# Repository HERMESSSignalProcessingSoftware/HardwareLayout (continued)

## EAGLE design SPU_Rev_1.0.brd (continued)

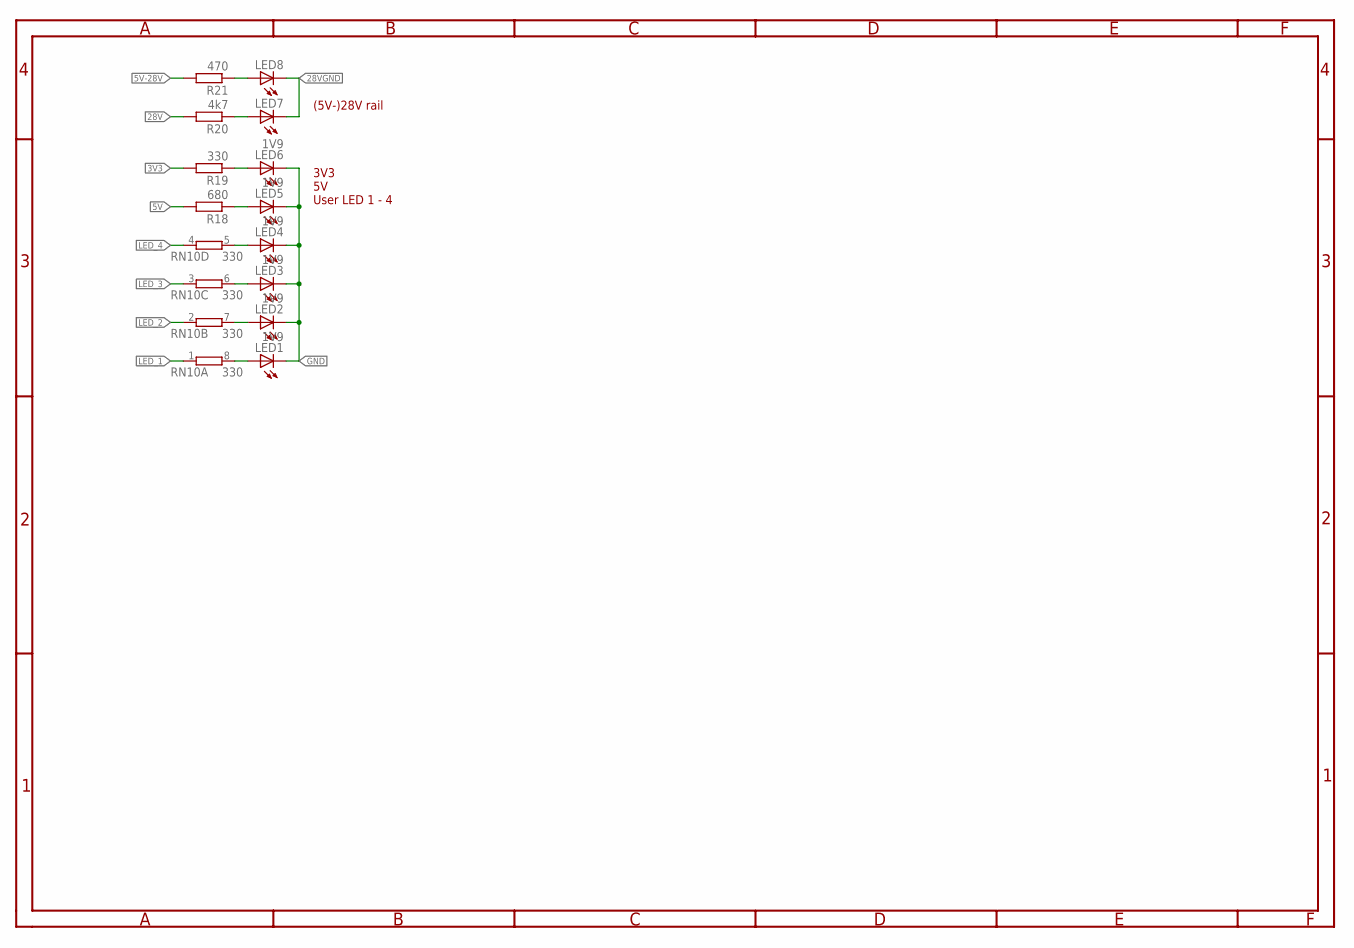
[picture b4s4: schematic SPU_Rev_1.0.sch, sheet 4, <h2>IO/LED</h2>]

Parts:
LED1, LED2, LED3, LED4, LED5, LED6: 1V9; CHIP-LED0603
LED7, LED8: LEDCHIP-LED0603; CHIP-LED0603
R18: 680; R0805
R19: 330; R0805
R20: 4k7; R0805
R21: 470; R0805
RN10: 330; EXBS8V

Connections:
3V3: R19.2; also elsewhere on the board
5V: R18.2; also elsewhere on the board
5V-28V: R21.2; also elsewhere on the board
28V: R20.2; also elsewhere on the board
28VGND: LED7.C, LED8.C; also elsewhere on the board
GND: LED1.C, LED2.C, LED3.C, LED4.C, LED5.C, LED6.C; also elsewhere on the board
LED_1: RN10.1; also elsewhere on the board
LED_2: RN10.2 (1); also elsewhere on the board
LED_3: RN10.3 (1); also elsewhere on the board
LED_4: RN10.4 (1); also elsewhere on the board
unnamed: LED1.A, RN10.8 (2)
unnamed: LED2.A, RN10.7 (2)
unnamed: LED3.A, RN10.6 (2)
unnamed: LED4.A, RN10.5 (2)
unnamed: LED5.A, R18.1
unnamed: LED6.A, R19.1
unnamed: LED7.A, R20.1
unnamed: LED8.A, R21.1

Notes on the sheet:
(5V-)28V rail 3V3 5V User LED 1 - 4

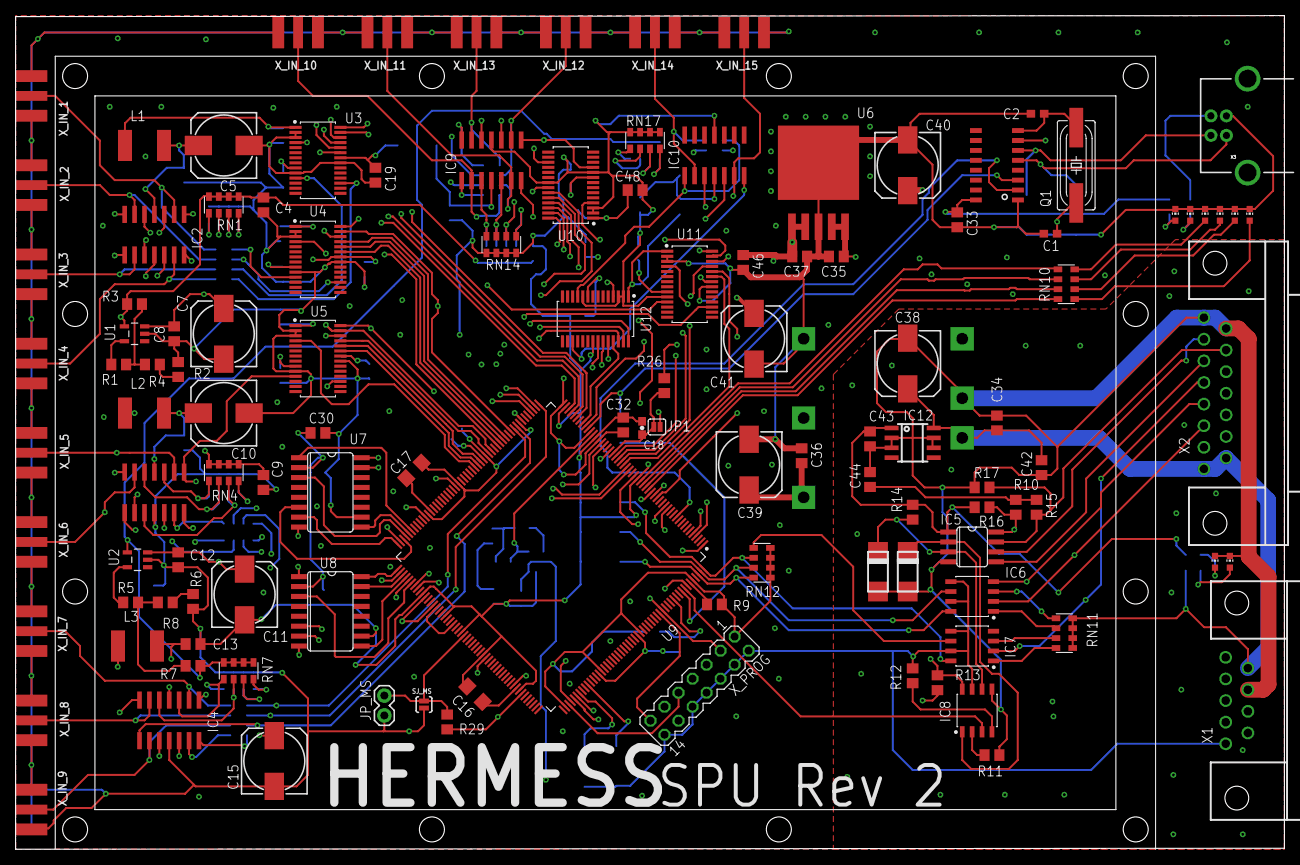
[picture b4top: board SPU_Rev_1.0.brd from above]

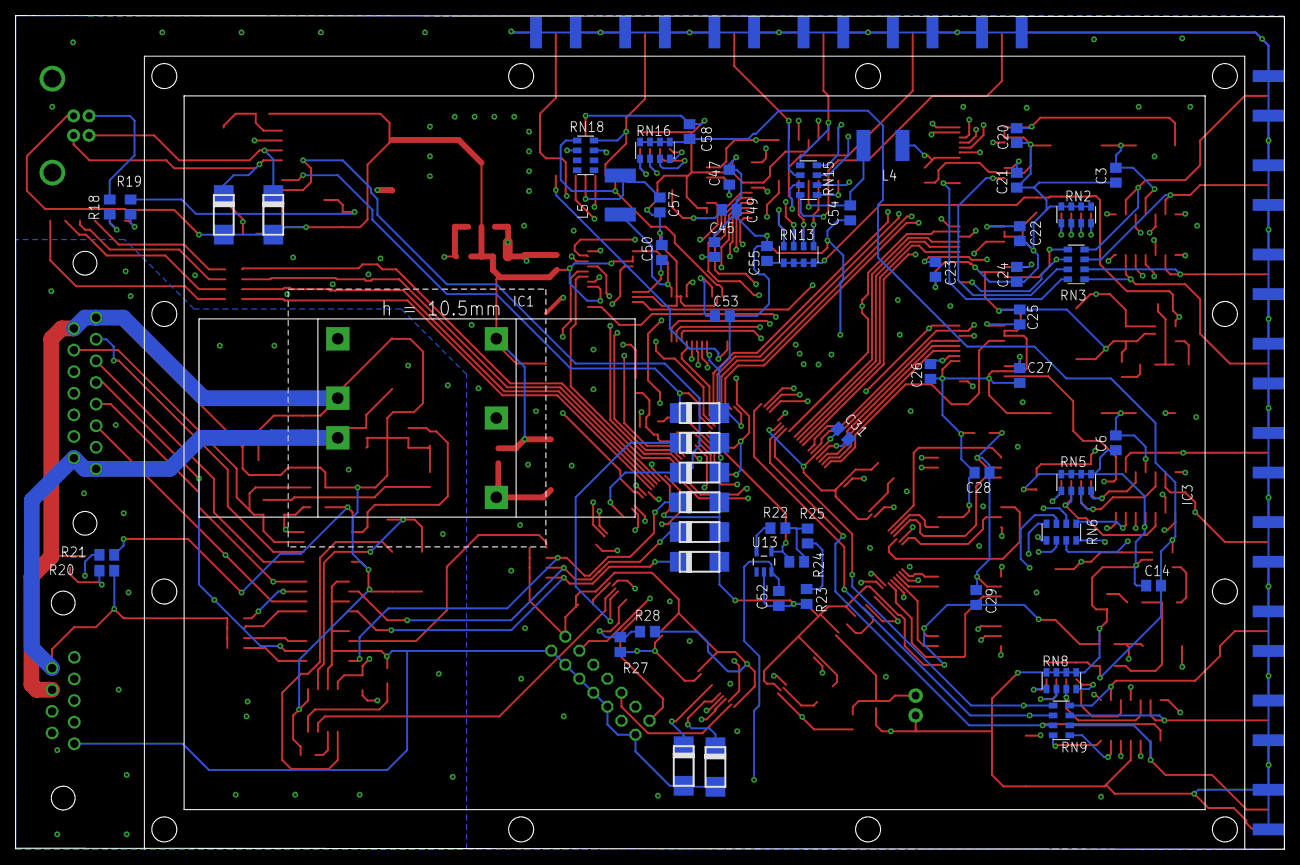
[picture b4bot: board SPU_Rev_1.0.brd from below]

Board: 4 copper layers, 162.6 x 106.8 mm, 176 parts (58 on the bottom side), 188 nets.

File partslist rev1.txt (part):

Partlist

Exported from Blade.brd at 25.03.2020 16:29

EAGLE Version 9.6.0 Copyright (c) 1988-2020 Autodesk, Inc.

Assembly variant: 

Part     Value                      Package                    Library              Position (mil)        Orientation

C1       22p                        C0603                      rcl                  (5220 3105)           R180
C2       22p                        C0603                      rcl                  (5155 3710)           R180
C3       10n                        C0805                      rcl                  (850 3400)            MR90
C4       10u                        C0805                      rcl                  (1250 3250)           R90
C5       10u                        153CLV-0810                rcl                  (1050 3550)           R180
C6       10n                        C0805                      rcl                  (850 2050)            MR90
C7       4u7                        153CLV-0810                rcl                  (1050 2600)           R90
C8       10n                        C0805                      rcl                  (800 2600)            R90
C9       10u                        C0805                      rcl                  (1250 1850)           R90
C10      10u                        153CLV-0810                rcl                  (1050 2200)           R180
C11      4u7                        153CLV-0810                rcl                  (1155 1285)           R90
C12      10n                        C0805                      rcl                  (820 1460)            R90
C13      10n                        C0805                      rcl                  (895 1035)            R180
C14      10u                        C0805                      rcl                  (660 1330)            MR0
C15      10u                        153CLV-0810                rcl                  (1305 445)            R90
C16      2.2u                       C1206                      rcl                  (2317.67766 782.32222) R315
C17      2.2u                       C1206                      rcl                  (2009.39333 1910.60655) R225
C18      100n                       0603-CAP                   aSparkFun            (3160 2125)           R90
C19      100n                       C0805                      rcl                  (1815 3400)           R270
C20      100n                       C0805                      rcl                  (1350 3600)           MR270
C21      1u                         C0805                      rcl                  (1350 3375)           MR270
C22      100n                       C0805                      rcl                  (1335 3105)           MR270
C23      100n                       C0805                      rcl                  (1760 2925)           MR270
C24      1u                         C0805                      rcl                  (1350 2900)           MR270
C25      100n                       C0805                      rcl                  (1335 2685)           MR90
C26      100n                       C0805                      rcl                  (1785 2410)           MR270
C27      1u                         C0805                      rcl                  (1335 2390)           MR270
C28      100n                       C0805                      rcl                  (1525 1900)           MR180
C29      100n                       C0805                      rcl                  (1555 1270)           MR270
C30      100n                       C0805                      rcl                  (1525 2100)           R0
C31      100n                       C0805                      rcl                  (2225 2095)           MR135
C32      100n                       C0805                      rcl                  (3065 2140)           R90
C33      100n                       C0805                      rcl                  (4750 3175)           R270
C34      100n                       C0805                      rcl                  (4950 2150)           R270
C35      100n                       C0805                      rcl                  (4140 2990)           R0
C36      100n                       C0805                      rcl                  (3965 1985)           R270
C37      100n                       C0805                      rcl                  (3955 2990)           R180
C38      10u                        153CLV-0810                rcl                  (4500 2450)           R270
C39      10u                        153CLV-0810                rcl                  (3700 1940)           R270
C40      10u                        153CLV-0810                rcl                  (4500 3450)           R270
C41      10u                        153CLV-0810                rcl                  (3725 2575)           R90
C42      100n                       C0805                      rcl                  (5175 1925)           R90
C43      100n                       C0805                      rcl                  (4310 2070)           R270
C44      ~0                         C0805                      rcl                  (4310 1865)           R90
C45      100n                       C0805                      rcl                  (2875 3025)           MR90
C46      100n                       C0805                      rcl                  (3670 2960)           R270
C47      1u                         C0805                      rcl                  (2800 3390)           MR90
C48      100n                       C0805                      rcl                  (3125 3325)           R0
C49      100n                       C0805                      rcl                  (2800 3225)           MR0
C50      1u                         C0805                      rcl                  (3140 3010)           MR90
C52      10n                        C0805                      rcl                  (2550 1265)           MR90
C53      1u                         C0805                      rcl                  (2835 2690)           MR0
C54      10n                        C0805                      rcl                  (2190 3210)           MR90
C55      10u                        C0805                      rcl                  (2610 3005)           MR270
C57      10n                        C0805                      rcl                  (3150 3250)           MR90
C58      10u                        C0805                      rcl                  (3000 3620)           MR270
D1       3V6                        DMELF                      diodes               (5100 3200)           MR90
D2       3V6                        DMELF                      diodes               (5350 3200)           MR90
D3       3V6                        DMELF                      diodes               (2950 2200)           MR180
D4       3V6                        DMELF                      diodes               (2950 1900)           MR180
D5       6V                         DMELF                      diodes               (4500 1400)           R90
D6       6V                         DMELF                      diodes               (4350 1400)           R90
D7       3V6                        DMELF                      diodes               (2950 1750)           MR180
D8       3V6                        DMELF                      diodes               (2950 1450)           MR180
D9       3V6                        DMELF                      diodes               (2950 1600)           MR180
D10      3V6                        DMELF                      diodes               (2950 2050)           MR180
IC1      THN10-2411WIR              THL_20WI_SERIES            traco_thl_tel_series (4375 2175)           MR90
IC2      MCP6064-E/SL               SO14                       linear               (700 3100)            R180
IC3      MCP6064-E/SL               SO14                       linear               (700 1800)            R180
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
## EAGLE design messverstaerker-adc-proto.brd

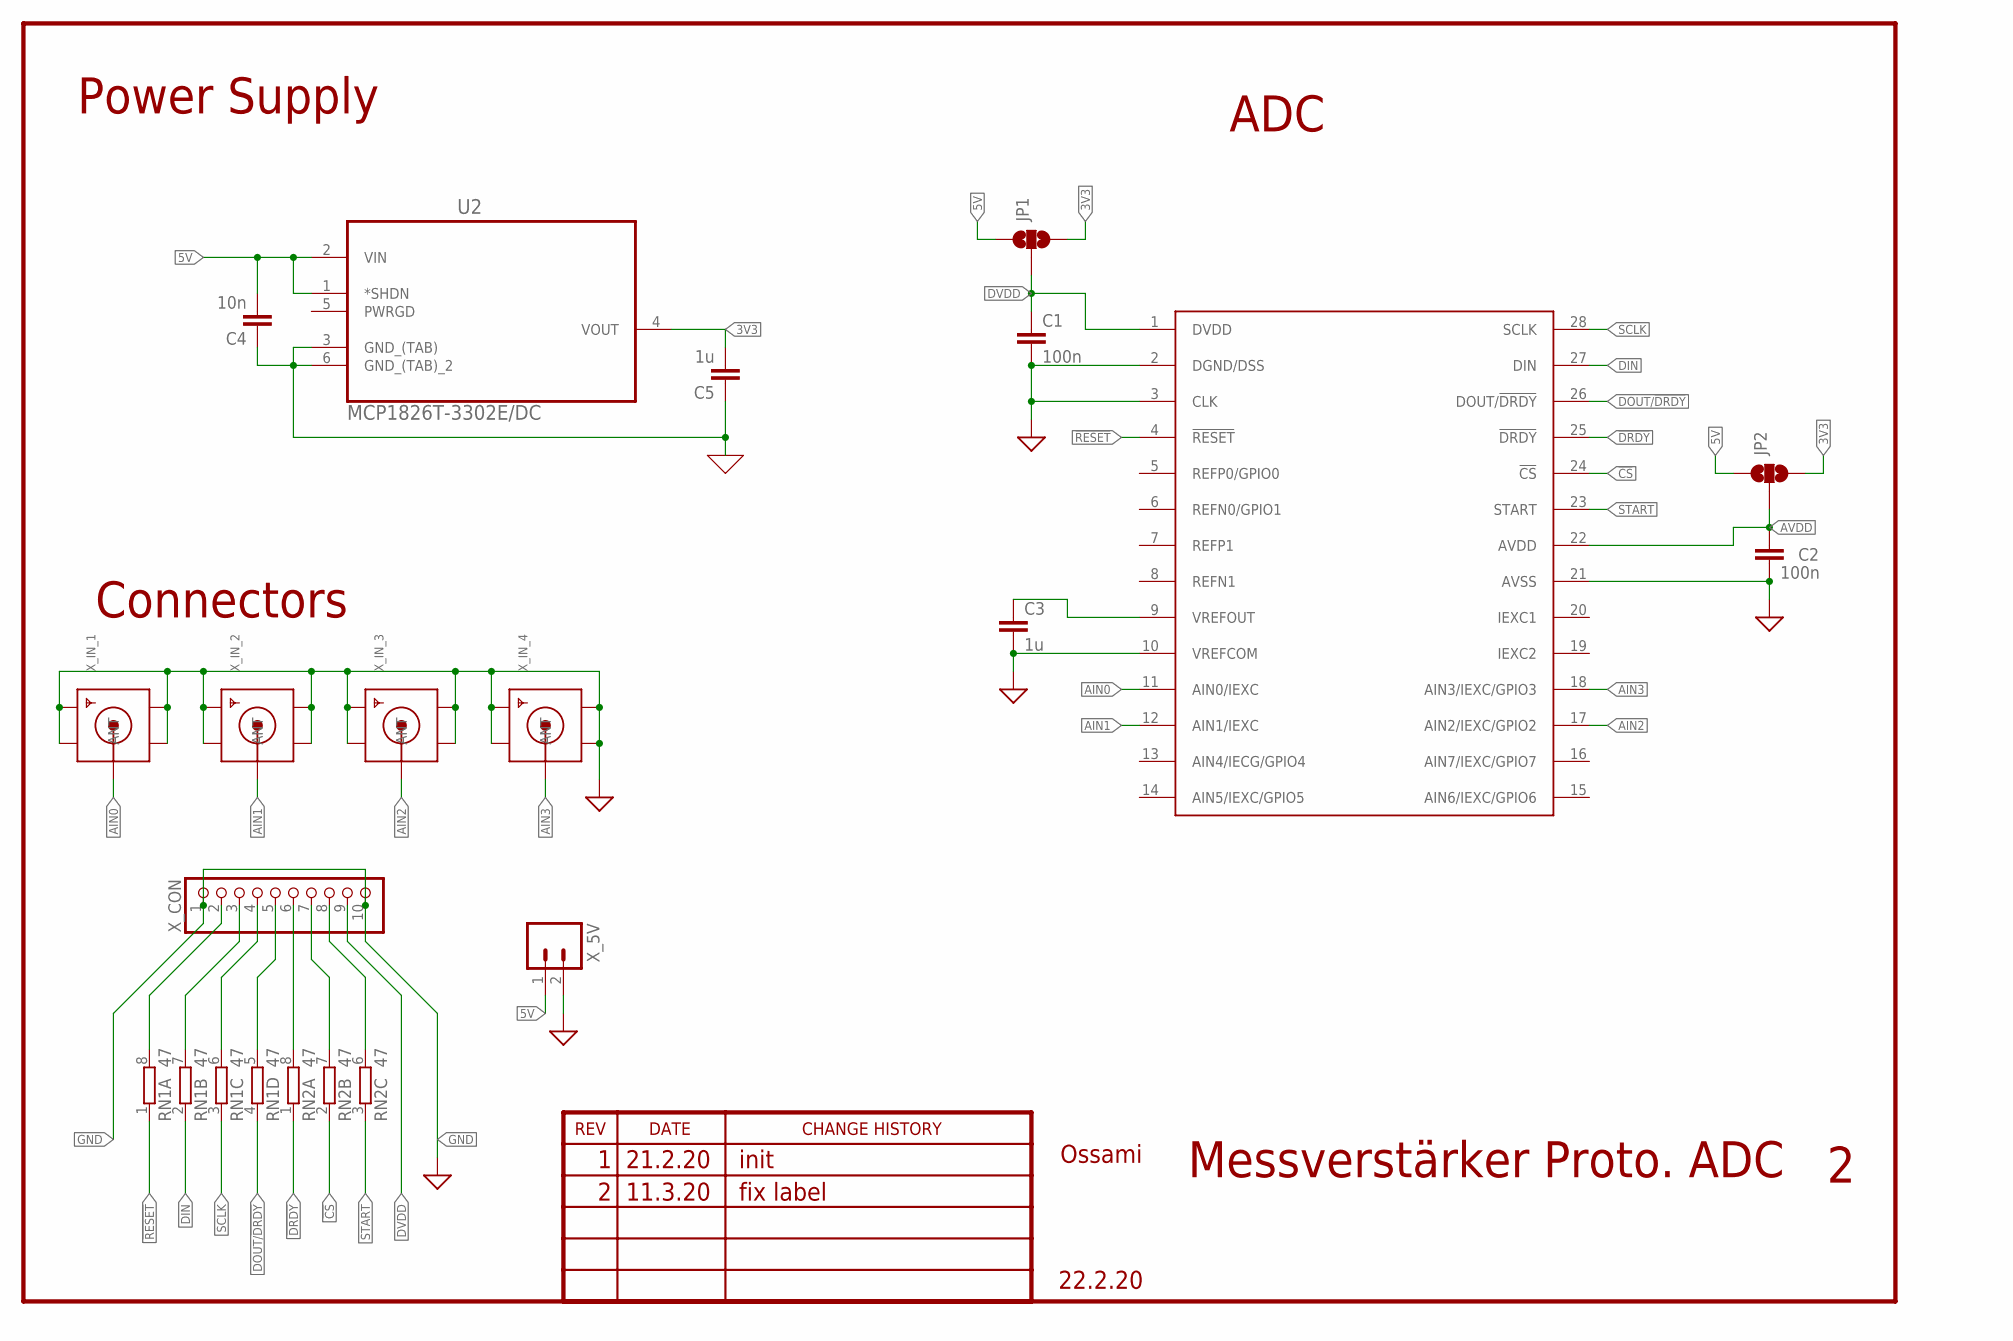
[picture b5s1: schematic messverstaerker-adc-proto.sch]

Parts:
C1, C2: 100n; C0805
C3, C5: 1u; C0805
C4: 10n; C0805
JP1, JP2: JUMPER-SMT_3_NO_NO-SILK; SMT-JUMPER_3_NO_NO-SILK
RN1, RN2: 47; EXBS8V
U1: ADS1148QPWRQ1; TSSOP28
U2: MCP1826T-3302E/DC; SOT230P700X180-6N
X_5V: M02LOCK; 1X02_LOCK
X_CON: PINHD-1X10; 1X10-BIG
X_IN_1, X_IN_2, X_IN_3, X_IN_4: SMACONNECTOR_EDGE; SMA_EDGELAUNCH

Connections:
0: C4.1, C5.1, U2.3 (GND_(TAB)), U2.6 (GND_(TAB)_2)
3V3: C5.2, JP1.3, JP2.3, U2.4 (VOUT)
5V: C4.2, JP1.1, JP2.1, U2.1 (*SHDN), U2.2 (VIN), X_5V.1
!CS: RN2.2 (1), U1.24 (!CS)
!DRDY: RN2.1, U1.25 (!DRDY)
!RESET: RN1.1, U1.4 (!RESET)
AIN0: U1.11 (AIN0/IEXC), X_IN_1.P (ANT)
AIN1: U1.12 (AIN1/IEXC), X_IN_2.P (ANT)
AIN2: U1.17 (AIN2/IEXC/GPIO2), X_IN_3.P (ANT)
AIN3: U1.18 (AIN3/IEXC/GPIO3), X_IN_4.P (ANT)
AVDD: C2.1, JP2.2, U1.22 (AVDD)
DIN: RN1.2 (1), U1.27 (DIN)
DOUT/!DRDY: RN1.4 (1), U1.26 (DOUT/!DRDY)
DVDD: C1.1, JP1.2, U1.1 (DVDD), X_CON.9
GND: C1.2, C2.2, C3.2, U1.2 (DGND/DSS), U1.3 (CLK), U1.10 (VREFCOM), U1.21 (AVSS), X_5V.2, X_CON.1, X_CON.10, X_IN_1.GND@1 (GND4), X_IN_1.GND@2 (GND3), X_IN_1.GND@3 (GND2), X_IN_1.GND@4 (GND1), X_IN_2.GND@1 (GND4), X_IN_2.GND@2 (GND3), X_IN_2.GND@3 (GND2), X_IN_2.GND@4 (GND1), X_IN_3.GND@1 (GND4), X_IN_3.GND@2 (GND3), X_IN_3.GND@3 (GND2), X_IN_3.GND@4 (GND1), X_IN_4.GND@1 (GND4), X_IN_4.GND@2 (GND3), X_IN_4.GND@3 (GND2), X_IN_4.GND@4 (GND1)
unnamed: RN1.5 (2), X_CON.5
unnamed: C3.1, U1.9 (VREFOUT)
unnamed: RN2.8 (2), X_CON.6
unnamed: RN2.7 (2), X_CON.7
unnamed: RN2.6 (2), X_CON.8
unnamed: RN1.6 (2), X_CON.4
unnamed: RN1.7 (2), X_CON.3
unnamed: RN1.8 (2), X_CON.2
SCLK: RN1.3 (1), U1.28 (SCLK)
START: RN2.3 (1), U1.23 (START)

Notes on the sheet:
Messverstärker Proto. ADC
Ossami
22.2.20
1 21.2.20 init
Power Supply
Connectors
ADC
2 11.3.20 fix label

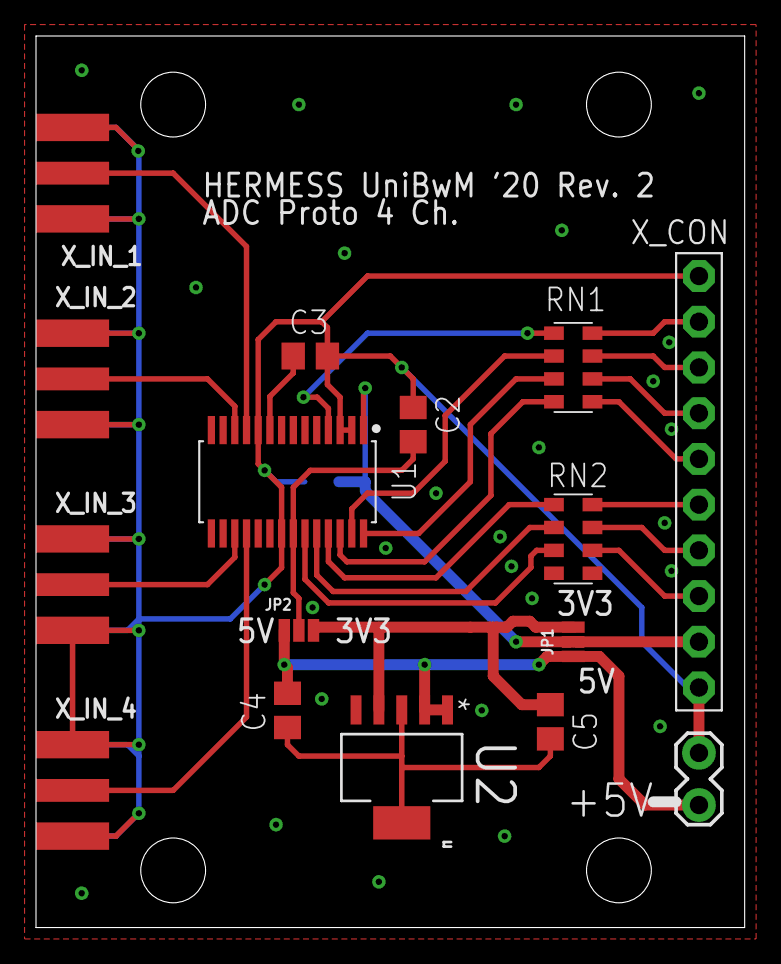
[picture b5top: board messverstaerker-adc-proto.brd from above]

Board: 2 copper layers, 39.4 x 49.5 mm, 17 parts (1 on the bottom side), 25 nets.

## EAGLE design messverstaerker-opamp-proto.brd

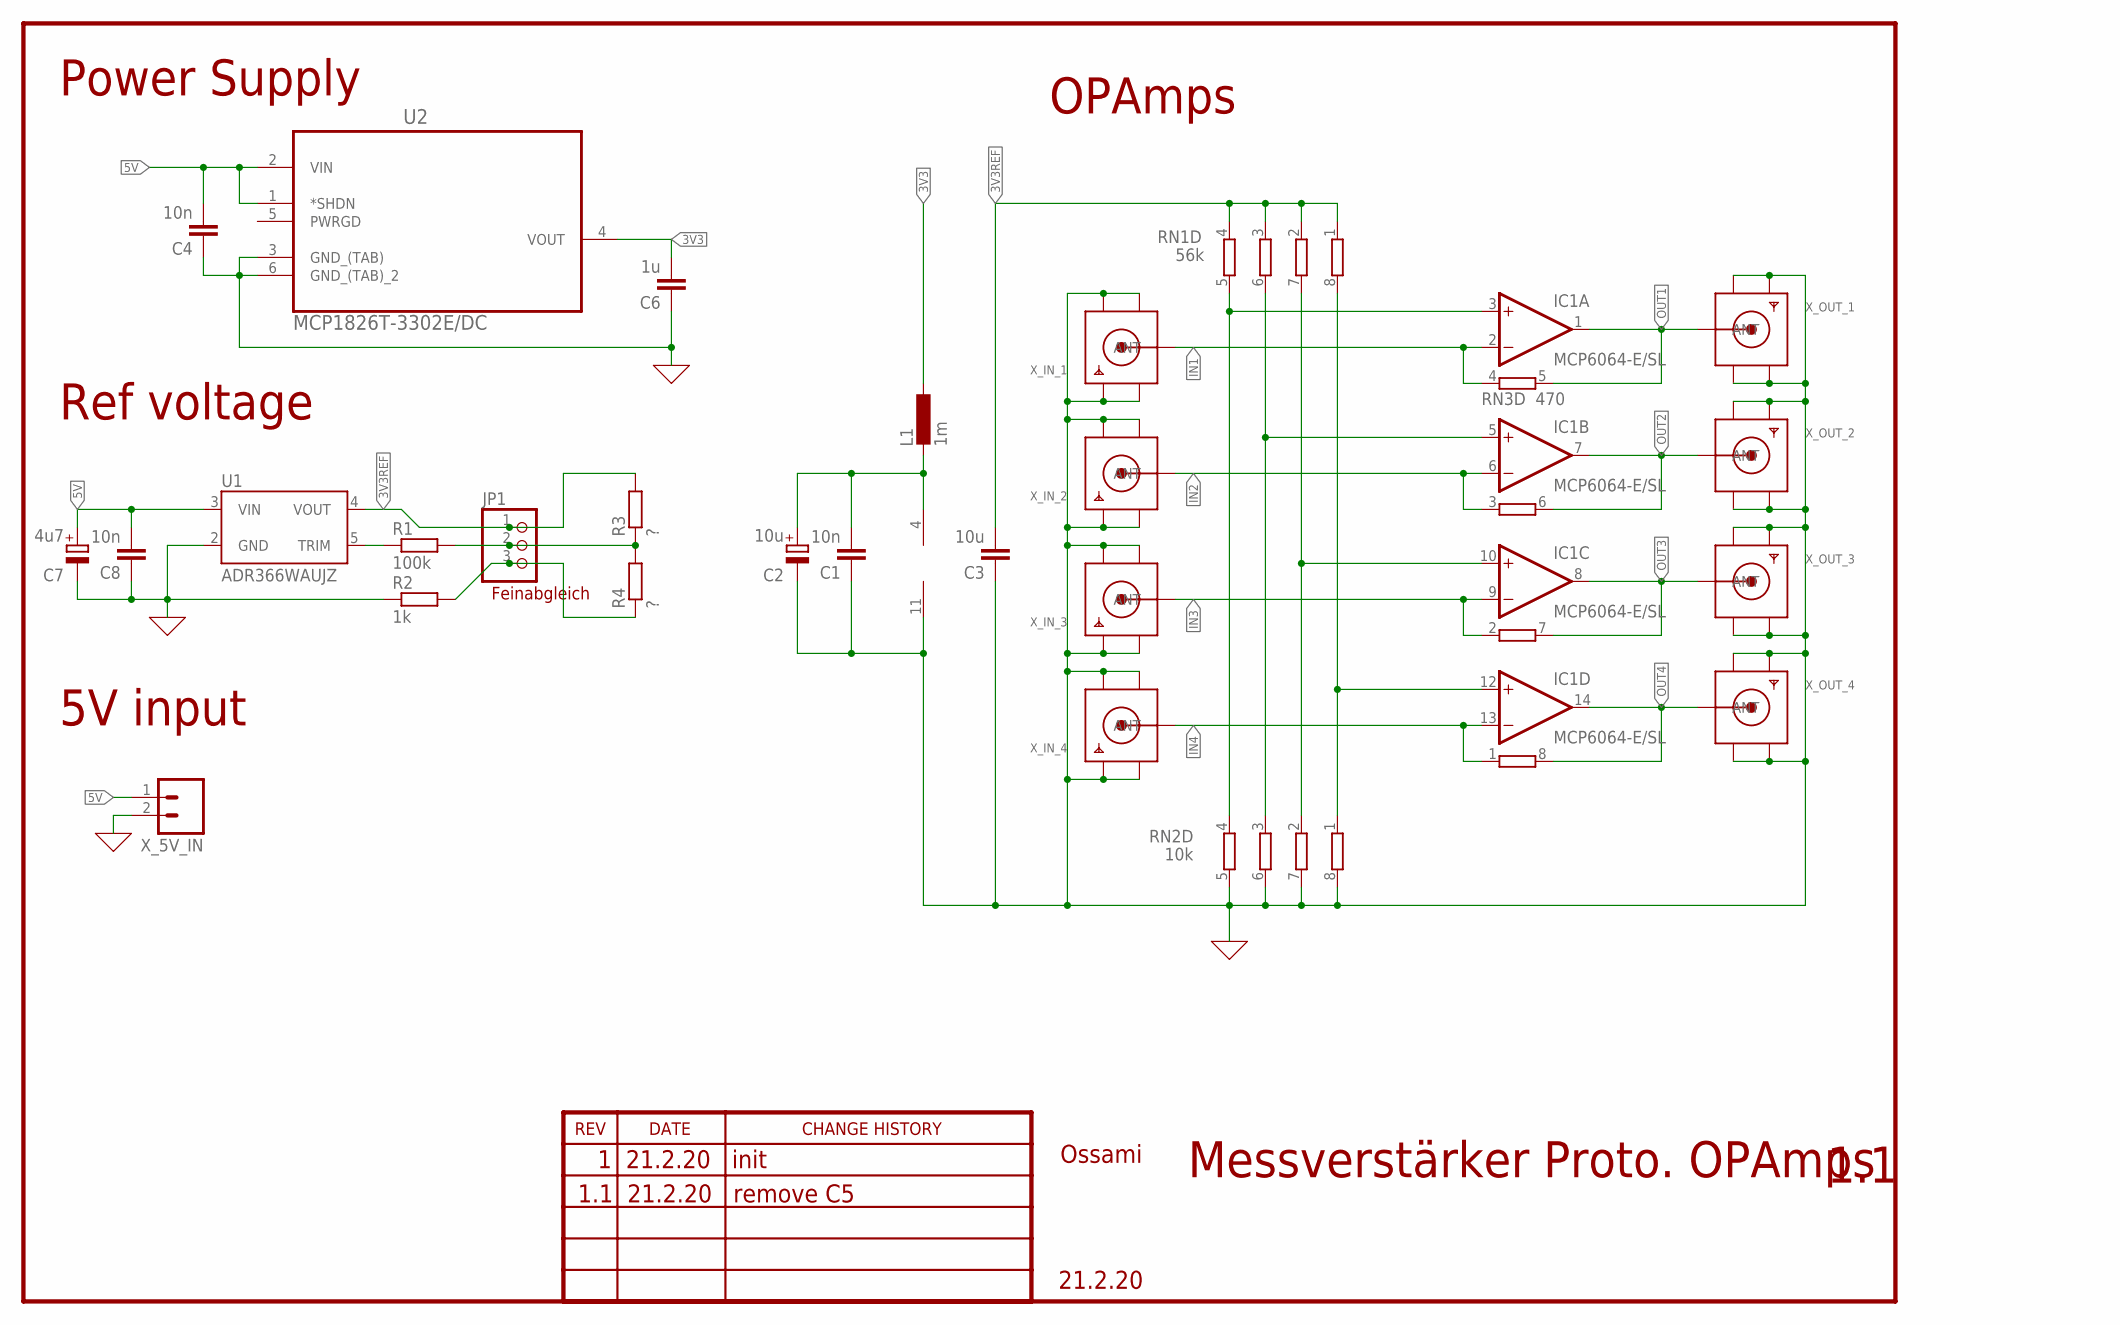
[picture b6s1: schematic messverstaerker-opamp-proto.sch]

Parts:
C1, C4, C8: 10n; C0805
C2: 10u; 153CLV-0810
C3: 10u; C0805
C6: 1u; C0805
C7: 4u7; 153CLV-0810
IC1: MCP6064-E/SL; SO14
JP1: PINHD-1X3; 1X03
L1: 1m; L5650M
R1: 100k; R0805
R2: 1k; R0805
R3, R4: ?; R0805
RN1: 56k; EXBS8V
RN2: 10k; EXBS8V
RN3: 470; EXBS8V
U1: ADR366WAUJZ; SOT23-5
U2: MCP1826T-3302E/DC; SOT230P700X180-6N
X_5V_IN: M02LOCK; 1X02_LOCK
X_IN_1, X_IN_2, X_IN_3, X_IN_4: SMACONNECTOR_EDGE; SMA_EDGELAUNCH
X_OUT_1, X_OUT_2, X_OUT_3, X_OUT_4: SMACONNECTOR_EDGE; SMA_EDGELAUNCH

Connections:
0: C1.1, C2.-, C3.1, C4.1, C6.1, C7.-, C8.1, IC1.11 (V-), R2.1, RN2.5 (2), RN2.6 (2), RN2.7 (2), RN2.8 (2), U1.2 (GND), U2.3 (GND_(TAB)), U2.6 (GND_(TAB)_2), X_5V_IN.2, X_IN_1.GND@1 (GND4), X_IN_1.GND@2 (GND3), X_IN_1.GND@3 (GND2), X_IN_1.GND@4 (GND1), X_IN_2.GND@1 (GND4), X_IN_2.GND@2 (GND3), X_IN_2.GND@3 (GND2), X_IN_2.GND@4 (GND1), X_IN_3.GND@1 (GND4), X_IN_3.GND@2 (GND3), X_IN_3.GND@3 (GND2), X_IN_3.GND@4 (GND1), X_IN_4.GND@1 (GND4), X_IN_4.GND@2 (GND3), X_IN_4.GND@3 (GND2), X_IN_4.GND@4 (GND1), X_OUT_1.GND@1 (GND4), X_OUT_1.GND@2 (GND3), X_OUT_1.GND@3 (GND2), X_OUT_1.GND@4 (GND1), X_OUT_2.GND@1 (GND4), X_OUT_2.GND@2 (GND3), X_OUT_2.GND@3 (GND2), X_OUT_2.GND@4 (GND1), X_OUT_3.GND@1 (GND4), X_OUT_3.GND@2 (GND3), X_OUT_3.GND@3 (GND2), X_OUT_3.GND@4 (GND1), X_OUT_4.GND@1 (GND4), X_OUT_4.GND@2 (GND3), X_OUT_4.GND@3 (GND2), X_OUT_4.GND@4 (GND1)
3V3: C6.2, L1.1, U2.4 (VOUT)
3V3REF: C3.2, JP1.1, R3.2, RN1.1, RN1.2 (1), RN1.3 (1), RN1.4 (1), U1.4 (VOUT)
5V: C4.2, C7.+, C8.2, U1.3 (VIN), U2.1 (*SHDN), U2.2 (VIN), X_5V_IN.1
IN1: IC1.2 (-IN), RN3.4 (1), X_IN_1.P (ANT)
IN2: IC1.6 (-IN), RN3.3 (1), X_IN_2.P (ANT)
IN3: IC1.9 (-IN), RN3.2 (1), X_IN_3.P (ANT)
IN4: IC1.13 (-IN), RN3.1, X_IN_4.P (ANT)
unnamed: IC1.3 (+IN), RN1.5 (2), RN2.4 (1)
unnamed: IC1.5 (+IN), RN1.6 (2), RN2.3 (1)
unnamed: IC1.10 (+IN), RN1.7 (2), RN2.2 (1)
unnamed: IC1.12 (+IN), RN1.8 (2), RN2.1
unnamed: R1.1, U1.5 (TRIM)
unnamed: C1.2, C2.+, IC1.4 (V+), L1.2
unnamed: JP1.2, R1.2, R3.1, R4.2
unnamed: JP1.3, R2.2, R4.1
OUT1: IC1.1 (OUT), RN3.5 (2), X_OUT_1.P (ANT)
OUT2: IC1.7 (OUT), RN3.6 (2), X_OUT_2.P (ANT)
OUT3: IC1.8 (OUT), RN3.7 (2), X_OUT_3.P (ANT)
OUT4: IC1.14 (OUT), RN3.8 (2), X_OUT_4.P (ANT)

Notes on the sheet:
Power Supply
5V input
Ref voltage
OPAmps
Messverstärker Proto. OPAmps
1.1
Ossami
21.2.20
1 21.2.20 init
1.1 21.2.20 remove C5
Feinabgleich

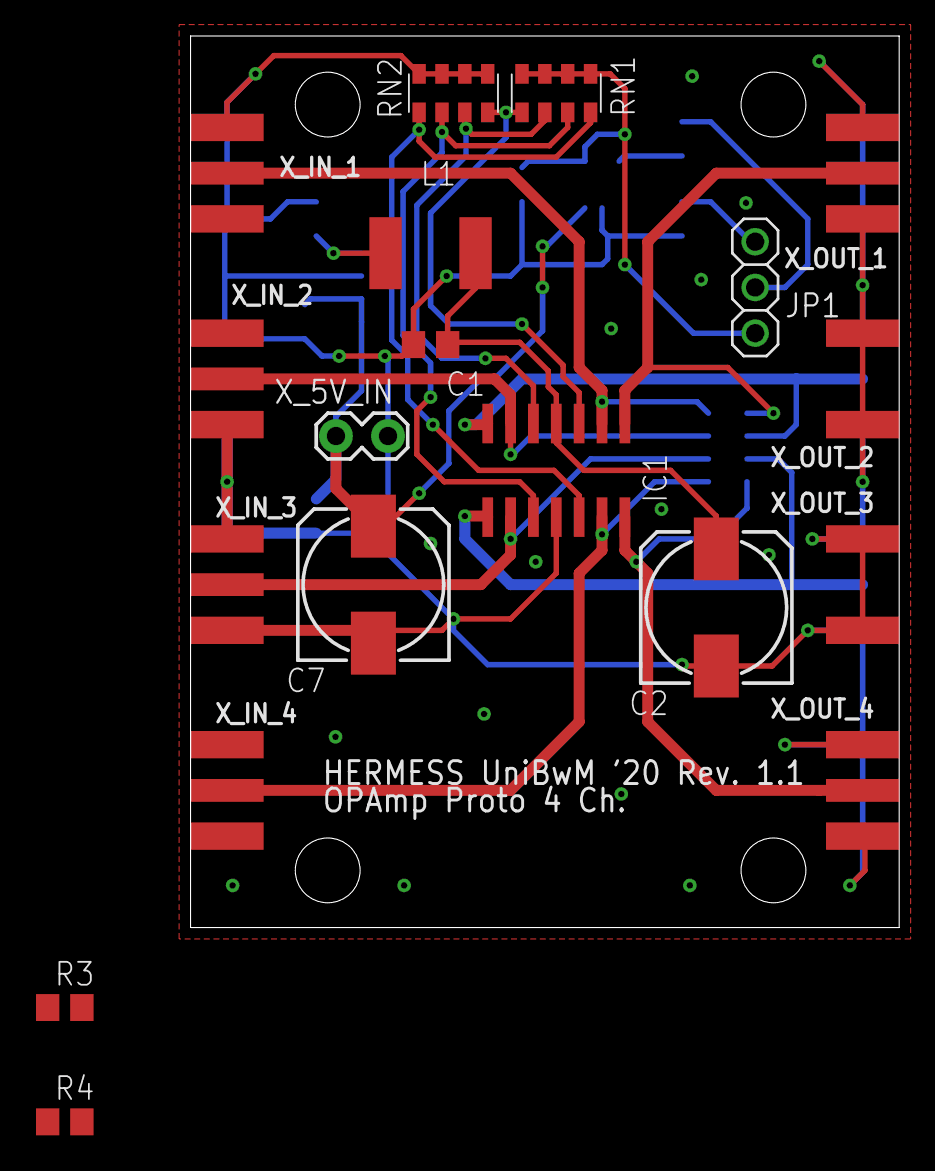
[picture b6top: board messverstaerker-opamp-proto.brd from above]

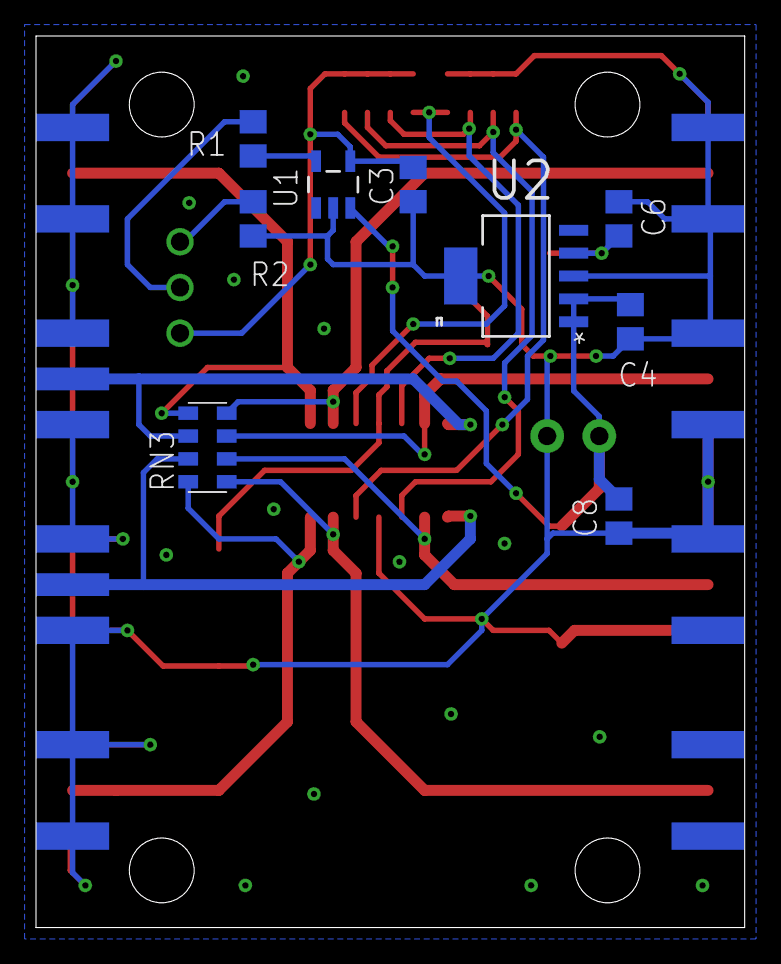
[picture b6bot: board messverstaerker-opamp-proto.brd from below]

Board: 2 copper layers, 39.4 x 49.5 mm, 28 parts (11 on the bottom side), 20 nets.

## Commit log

2020-03-19 initial push
2020-03-19 docs
2020-03-19 opto added
2020-03-19 cleanup
2020-03-22 RS422 opto galv isolation added
2020-03-22 rerouting
2020-03-23 ground vias
2020-03-23 ads added
2020-03-24 bom added, text cleanup
2020-03-24 finished routing Rev. 1
2020-03-25 Create libraries
2020-03-25 libs added
2020-03-25 partslist updated
2020-03-26 Pinout Image
2020-03-26 board image sw
2020-03-26 pinout in s/w
2020-03-28 schematics png/pdf
2020-03-31 Adding new images
2020-04-27 Werte Update
2020-04-29 flash footprint korrigiert
2020-04-29 led widerstand angepasst
2020-05-01 Widerstände Wert definiert
2020-05-03 interspu connector, ms select
    interspu connector added
    master/slave (solder)jumper added
2020-05-03 fusion360 sync
2020-05-06 Renamed to SPU_Rev_xx
2020-05-21 Revert "Renamed to SPU_Rev_xx"
    This reverts commit 304736c8d07f8b224d599abdd620e5674e37052e.
2020-05-25 zwischenstand
    NOT FINAL
2020-07-19 NOT final
2020-08-01 foo
    bar
2020-08-05 rev 2.1
2020-08-05 renamed to 2.1
2020-08-05 viafence STRUCT
2020-08-11 some routing
2020-08-11 Pins matched to Cube
    next step, autoroute (if possible)
2020-08-11 cleanup autoroute 1/inf
2020-08-11 fix autoroute 2/inf
2020-08-11 finished routing
2020-08-18 finalized silkscreen
2020-08-24 airwire fixed (2x)
2020-09-07 microsd added
2020-12-20 added LWL OUT
    added LWL OUT jack
2020-12-31 added LWL IN
    added LWL IN
2021-01-05 connector board
2021-01-05 Added PT100 ADC R/C values
2021-01-08 RS422 confirmed
    RS422 driver functionality plus optocouplers tested and confirmed
2021-01-10 HERMESS COIN
    Adding HERMESS Coin REV 1
2021-01-10 Adding Images and GIMP Project
2021-01-11 Adding Coin bord and images, redesign started
2021-01-11 Opto Pull-up adjusted
2021-01-11 Update of Coin, just GIMP
2021-01-12 Changed Logo, just grafik works
2021-01-13 Minor adjustments
    adjusted zener values, added optinal trimresistors for voltage setting.
2021-01-13 Coin QR final final version
2021-01-13 new coin
2021-01-14 Clean up
2021-01-16 Update Bestellung.xlsx, HERMESS - Spaß coin fehlt noch.
2021-02-01 Adding reverse "We are not floemess"
2021-02-01 adding images for funny coin
2021-02-01 Adding FLO/HERMESS coin, just 4 fun
2021-03-30 Cleanup for new design
2021-03-31 Adds smf2 lib
2021-04-04 Adds STAMPs
2021-04-04 Almost final sch
2021-04-09 Minor changes
2021-04-14 Adds changes as of Grimsmann
2021-05-06 First STAMP layout
2021-05-12 Before autoroute
2021-05-18 Pre DRC
2021-05-23 Post DRC
2021-06-01 Finishes Airwires
2021-06-03 Adds production files
2021-07-01 Adds suggestions
2021-07-05 Improves labelling
2021-07-23 Even more suggestions
2021-09-25 Adding updated SMF2 lib\nAdding descriptions to lib
2021-09-27 Updating .gitignore: Ignoring testfiles
2021-10-17 Adding FTDI FT2232HL Updating SMF2.lbr TODO: - Rename lib so a more percise name - Check schematic before production!
2021-11-12 Updates schematics
2021-11-12 Fixes LEDs
2021-11-16 Finished Placement
2021-11-16 After AR 97.8%
2021-11-17 Working copy of R.G.
    Reordered parts, not final yet
2021-11-18 Adding Jlcpcb drc file
2021-11-18 During work commit
2021-11-19 During work commit Reorderd RXSM interface
2021-11-19 Schematic: changed names from STAMP2 - STMAP6 to STAMPN_ADC_SG/TEMP Bord: Adding names for more readabilty.
2021-11-19 End of day commit Schematic: Removed renaming error Bord: Placed and routed Stamp 2
2021-11-20 Ignoring local KiCAD folder
2021-11-20 Mid day commit Moved Stamp 3 -5, continue with stamp 6, currently disabled airwires: GND, 3v3 Added names to top and bottom rerouted 4Mhz clk
2021-11-20 Routed all signals and voltages End of day commit TODO: GND connection Adding WE - XTAL Eagle lib Update schematic: Adding XTAL Bord: routed
    NOTE: DRC not ok
2021-11-21 Adding vias 54 airwires
2021-11-21 Routing completed DRC: Run successfully Adding via fences Resolved grounding problems NOTE: USB Port position changed NOTE: Run ratsnest before generating gerber files
2021-11-21 Routing completed DRC: Run successfully Adding via fences Resolved grounding problems NOTE: USB Port position changed NOTE: Run ratsnest before generating gerber files
    NOTE: Second commit, same topic due to previous staged changes.
2021-11-21 Minor changes
    - XTAL from AUX to MAIN
    - Removes authors
    - Adds interface measurements
    - Fixes Airwire / Wirestub
2021-11-22 Minor changes Minimal increased grounding plate on top layer Removed wirestubs DRC run: successful
2021-11-26 Adds orders
2021-12-16 Update FTDI template
